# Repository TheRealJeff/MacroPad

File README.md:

# MacroPad
This page outlines the MacroPad V1 keyboard project. This keyboard is a custom made 4x3 (rxc) with hotswap MX style switches based on the ATMEGA32U4 MCU platform. It is powered by a built-in USB-C connector and uses a custom firmware designed and uploaded with QMK (QMK MSYS and QMK Toolbox). All the required files for PCB, Mech and Firmware are found here.

- '\PCB': kicad, BOM, GERBERS files
- '\3D': Mech design files
- '\firmware': keymaps, configs and hex files

## PCB Design
The PCB was fully designed with KiCAD 7, uses the keyswitch libraries from [ai03 Custom Keyboard](https://wiki.ai03.com/books/pcb-design) and is based on the design from [Masterzen's Blog](https://www.masterzen.fr/2020/05/03/designing-a-keyboard-part-1/).

The keyboard uses an ATMEGA32U4 to receive inputs from a 4x3 key switch matrix. The keyboard uses a USB-C over a USB 2.0 interface for power and data. The switches have Kailh hot swap sockets for easy swapping of the key switches.

## Mech Design
The keyboard has a basic enclosure designed to mainly give it a flat support for testing. It is mounted with 4 M2.5x4mm screws for stability. Currently, the key switches are only retained by the hot swap sockets.

## Firmware
QMK was used for the custom keymap (key switch layout).  Currently, the layout has the following keymap:
| ESC | DEL | 0 |
|-----|-----|---|
| 7   | 8   | 9 |
| 4   | 5   | 6 |
| 1   | 2   | 3 |

### Keyboard Programming
Download QMK MSYS and QMK Toolbox. Open QMK MSYS and follow the on screen instructions to download the necessary repos and drivers.

The `firmware\macropadv1` folder must be put in the `qmk_firmware\keyboards` folder downloaded and installed by QMK MSYS.

To create a new keymap, simply make a new folder in `macropadv1\keymap`, copy the default keymap file and modify it. In QMK MSYS, use the command `qmk compile -kb <keyboard> -km <keymap>` with the selected `keyboard` and `keymap`.

To upload the created `.hex` file, use QMK Toolbox. Connect the keyboard, and press on the reset button. The Toolbox window should display a "DFU Mode" message. At this point, select the `.hex` and flash the keyboard.

## Future Work
Future revisions will have the following updates:
- Use the RP2040 MCU
- LEDs
- Different key matrices
	- 1x2 for OSU
	- Numpad
	- TKL
	- Split keyboard layout (see ZSA Moonlander)
	- Alice Layout
- Better software update for keymaps
- Redesigned enclosure for plate mount switches

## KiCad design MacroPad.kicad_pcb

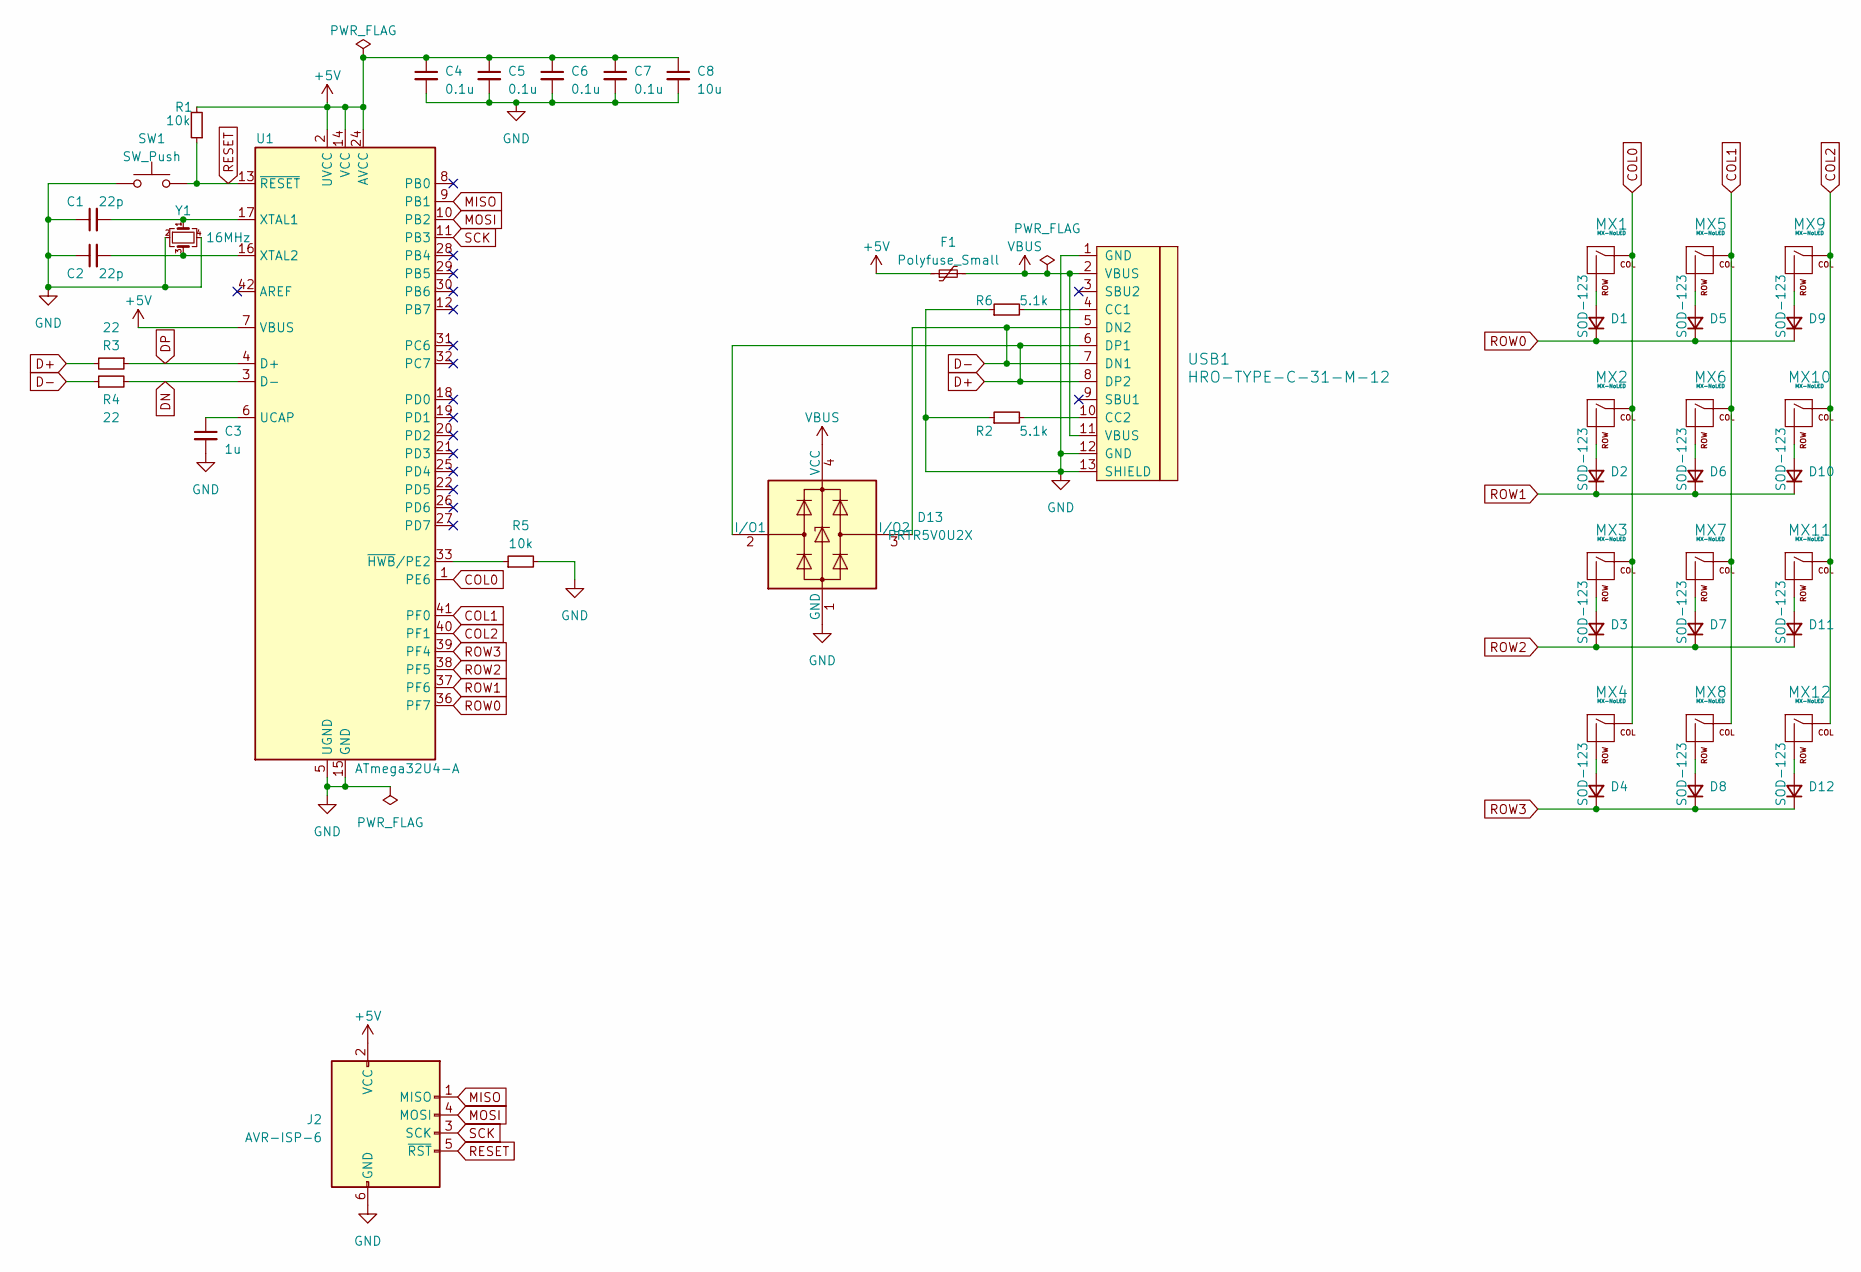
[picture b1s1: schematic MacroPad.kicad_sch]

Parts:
C1, C2: 22p; C_0805_2012Metric
C3: 1u; C_0805_2012Metric
C4, C5, C6, C7: 0.1u; C_0805_2012Metric
C8: 10u; C_0805_2012Metric
D1, D2, D3, D4, D5, D6, D7, D8, D9, D10, D11, D12: SOD-123; D_SOD-123
D13: PRTR5V0U2X; SOT-143
F1: Polyfuse_Small; Fuse_1206_3216Metric_Pad1.42x1.75mm_HandSolder
J2: AVR-ISP-6; Reset_Pretty-Mask
MX1, MX2, MX3, MX4, MX5, MX6, MX7, MX8, MX9, MX10, MX11, MX12: MX-NoLED; MXOnly-1U-Hotswap
R1, R5: 10k; R_0805_2012Metric
R2, R6: 5.1k; R_0805_2012Metric
R3, R4: 22; R_0805_2012Metric
SW1: SW_Push; SKQG-1155865
U1: ATmega32U4-A; TQFP-44_10x10mm_P0.8mm
USB1: HRO-TYPE-C-31-M-12; HRO-TYPE-C-31-M-12-HandSoldering
Y1: 16MHz; Crystal_SMD_3225-4Pin_3.2x2.5mm_HandSoldering

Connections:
+5V: C4.1, C5.1, C6.1, C7.1, C8.1, F1.1, J2.2 (VCC), R1.2, U1.2 (UVCC), U1.7 (VBUS), U1.14 (VCC), U1.24 (AVCC), U1.34 (VCC), U1.44 (AVCC)
COL0: MX1.1 (COL), MX2.1 (COL), MX3.1 (COL), MX4.1 (COL), U1.1 (PE6)
COL1: MX5.1 (COL), MX6.1 (COL), MX7.1 (COL), MX8.1 (COL), U1.41 (PF0)
COL2: MX9.1 (COL), MX10.1 (COL), MX11.1 (COL), MX12.1 (COL), U1.40 (PF1)
D+: D13.2 (I/O1), R3.2, USB1.6 (DP1), USB1.8 (DP2)
D-: D13.3 (I/O2), R4.1, USB1.5 (DN2), USB1.7 (DN1)
DN: R4.2, U1.3 (D-)
DP: R3.1, U1.4 (D+)
GND: C1.1, C2.1, C3.2, C4.2, C5.2, C6.2, C7.2, C8.2, D13.1 (GND), J2.6 (GND), R2.1, R5.2, R6.1, SW1.1, U1.5 (UGND), U1.15 (GND), U1.23 (GND), U1.35 (GND), U1.43 (GND), USB1.1 (GND), USB1.12 (GND), USB1.13 (SHIELD), Y1.2, Y1.4
MISO: J2.1 (MISO), U1.9 (PB1)
MOSI: J2.4 (MOSI), U1.10 (PB2)
unnamed: D1.2 (A), MX1.2 (ROW)
unnamed: D2.2 (A), MX2.2 (ROW)
unnamed: D3.2 (A), MX3.2 (ROW)
unnamed: D4.2 (A), MX4.2 (ROW)
unnamed: D5.2 (A), MX5.2 (ROW)
unnamed: D6.2 (A), MX6.2 (ROW)
unnamed: D7.2 (A), MX7.2 (ROW)
unnamed: D8.2 (A), MX8.2 (ROW)
unnamed: D9.2 (A), MX9.2 (ROW)
unnamed: D10.2 (A), MX10.2 (ROW)
unnamed: D11.2 (A), MX11.2 (ROW)
unnamed: D12.2 (A), MX12.2 (ROW)
unnamed: C3.1, U1.6 (UCAP)
unnamed: C1.2, U1.17 (XTAL1), Y1.1
unnamed: C2.2, U1.16 (XTAL2), Y1.3
unnamed: R5.1, U1.33 (~HWB/PE2)
unnamed: R6.2, USB1.4 (CC1)
unnamed: R2.2, USB1.10 (CC2)
RESET: J2.5 (~RST), R1.1, SW1.2, U1.13 (~RESET)
ROW0: D1.1 (K), D5.1 (K), D9.1 (K), U1.36 (PF7)
ROW1: D2.1 (K), D6.1 (K), D10.1 (K), U1.37 (PF6)
ROW2: D3.1 (K), D7.1 (K), D11.1 (K), U1.38 (PF5)
ROW3: D4.1 (K), D8.1 (K), D12.1 (K), U1.39 (PF4)
SCK: J2.3 (SCK), U1.11 (PB3)
VBUS: D13.4 (VCC), F1.2, USB1.2 (VBUS), USB1.11 (VBUS)

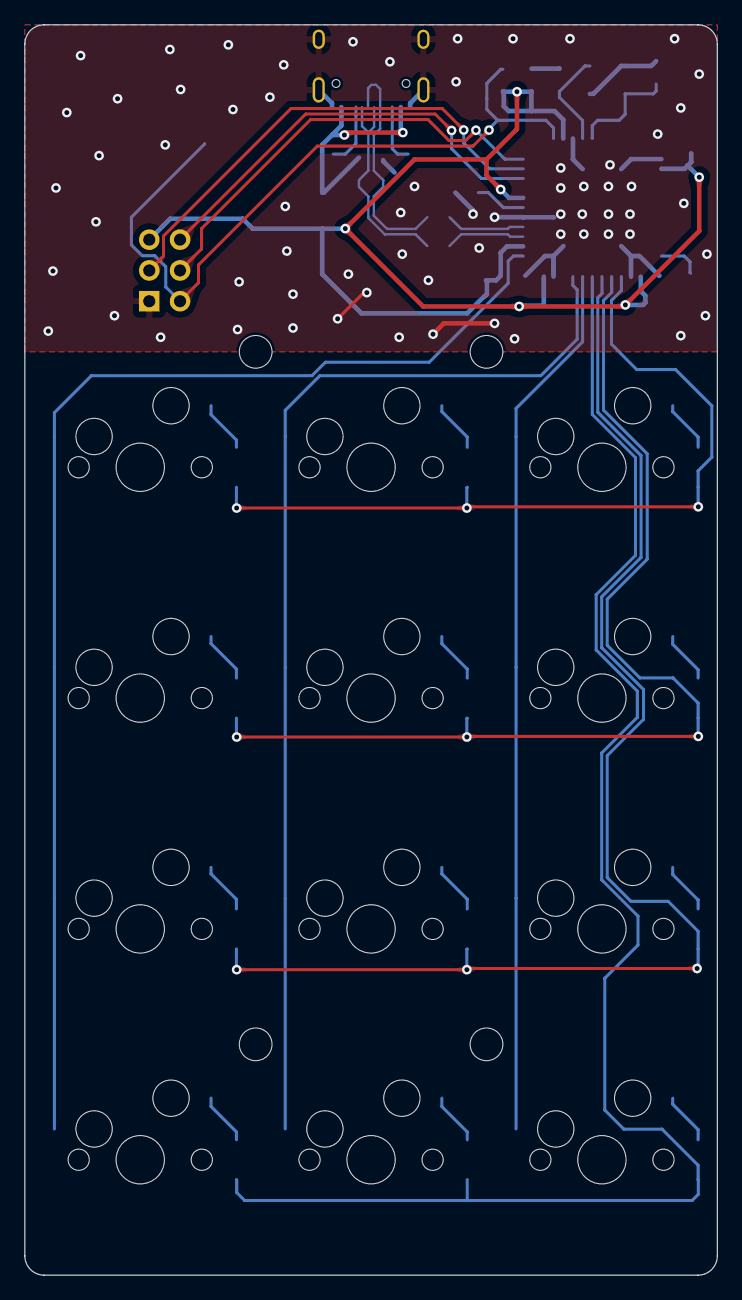
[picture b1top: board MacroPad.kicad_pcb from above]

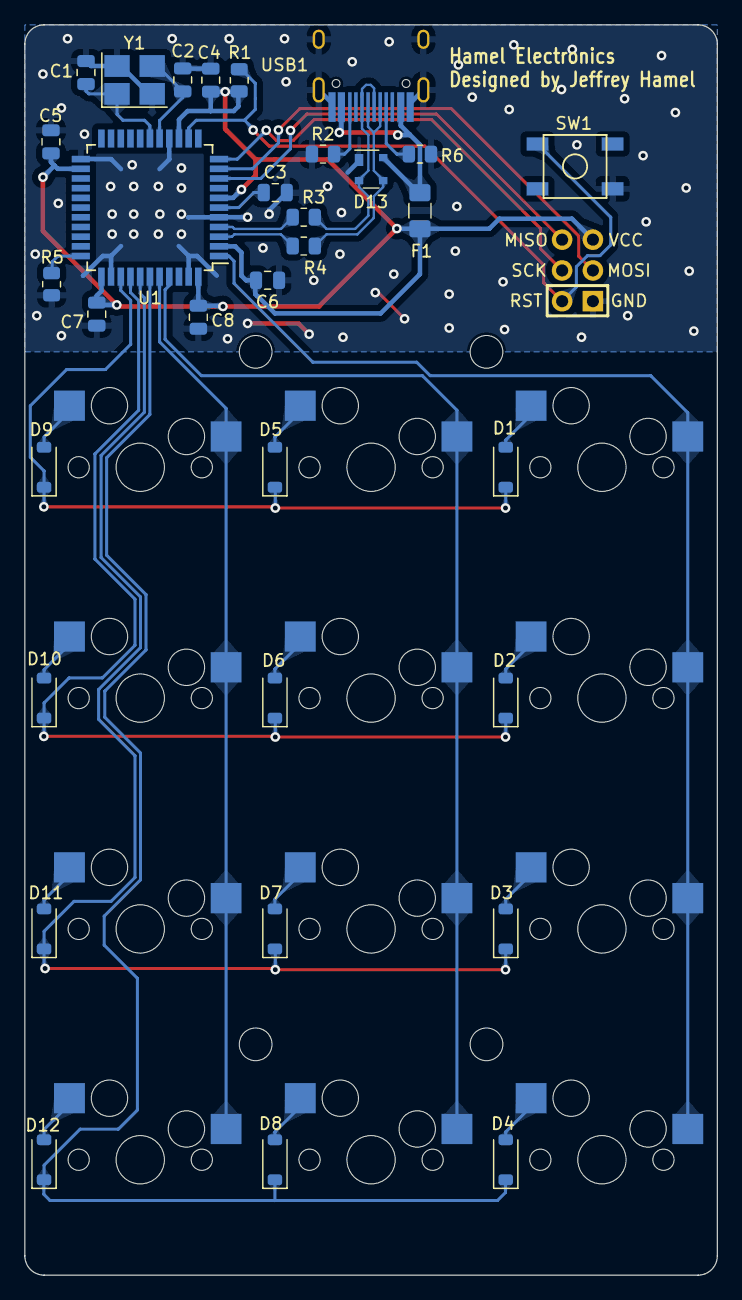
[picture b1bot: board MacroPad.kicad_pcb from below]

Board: 2 copper layers, 57.2 x 103.2 mm, 45 parts (33 on the bottom side), 36 nets.

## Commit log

2023-03-10 KiCAD project init
2023-03-10 Add submodules
2023-03-10 Added schematic and footprint libraries
2023-03-10 Finalized schematic
2023-03-10 Initial component placement
2023-03-11 added USB-C libraries
2023-03-11 reworked schematic, added footprint library for USB-C, improved component placement
2023-03-12 finished placement, routing and overall layout
2023-03-12 production files
2023-03-12 adding cart for later usage
2023-03-12 made macropad enclosure
2023-03-15 Added B. Silkscreen notes
2023-04-12 added firmware for qmk and updated 3D
2023-04-12 Update keymap table
2023-04-13 force enable NKRO and 1000Hz polling
2025-01-07 restructed folders and updated README
